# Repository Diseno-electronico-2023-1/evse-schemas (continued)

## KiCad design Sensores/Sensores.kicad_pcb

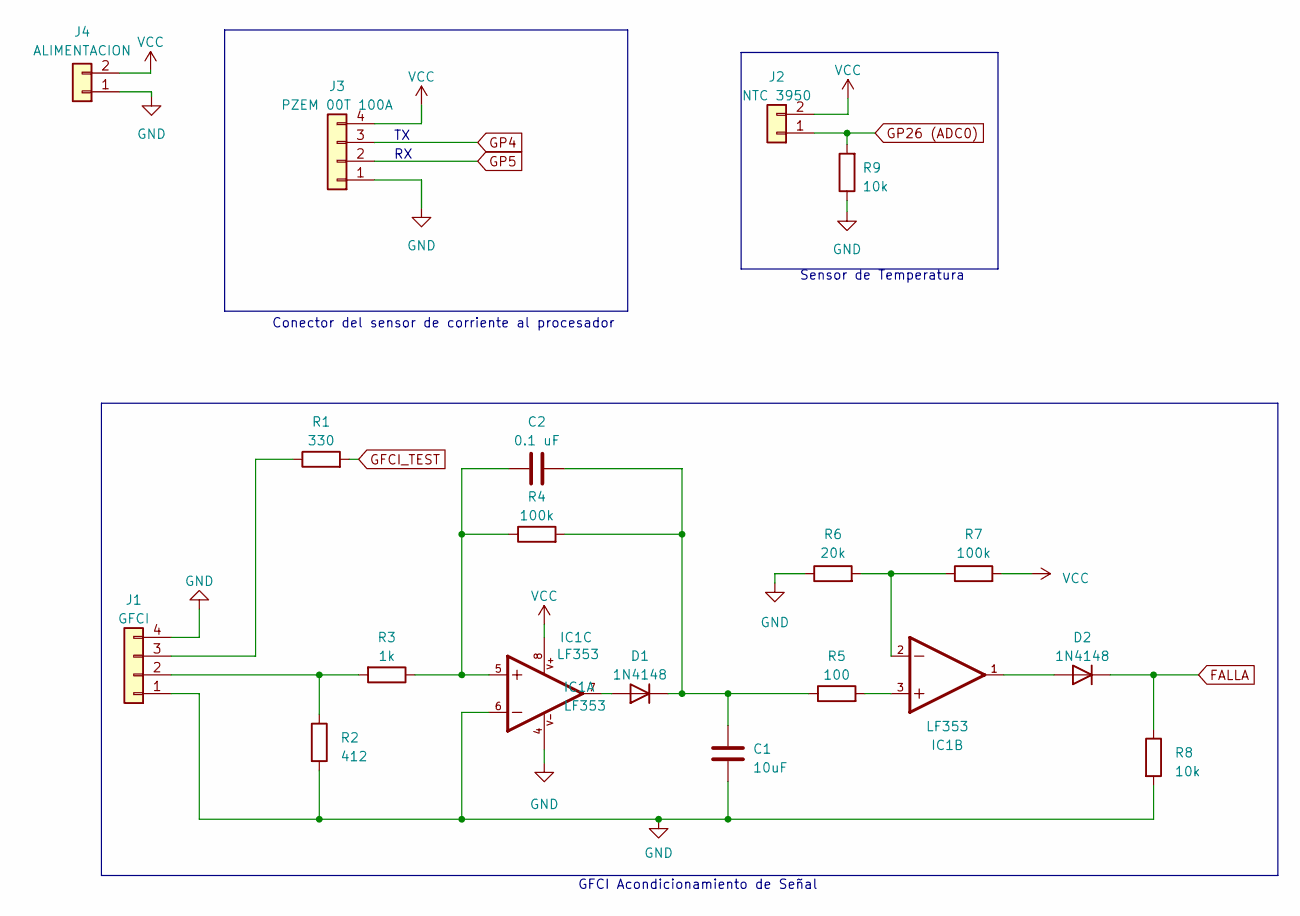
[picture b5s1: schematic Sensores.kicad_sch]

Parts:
C1: 10uF; C_0805_2012Metric_Pad1.18x1.45mm_HandSolder
C2: 0.1 uF; C_0805_2012Metric_Pad1.18x1.45mm_HandSolder
D1, D2: 1N4148; D_DO-35_SOD27_P7.62mm_Horizontal
IC1: LF353; DIL08
J1: GFCI; JST_EH_B4B-EH-A_1x04_P2.50mm_Vertical
J2: NTC 3950; JST_EH_B2B-EH-A_1x02_P2.50mm_Vertical
J3: PZEM 00T 100A; JST_EH_B4B-EH-A_1x04_P2.50mm_Vertical
J4: ALIMENTACION; JST_EH_B2B-EH-A_1x02_P2.50mm_Vertical
R1: 330; R_1206_3216Metric_Pad1.30x1.75mm_HandSolder
R2: 412; R_1206_3216Metric_Pad1.30x1.75mm_HandSolder
R3: 1k; R_1206_3216Metric_Pad1.30x1.75mm_HandSolder
R4, R7: 100k; R_1206_3216Metric_Pad1.30x1.75mm_HandSolder
R5: 100; R_1206_3216Metric_Pad1.30x1.75mm_HandSolder
R6: 20k; R_1206_3216Metric_Pad1.30x1.75mm_HandSolder
R8, R9: 10k; R_1206_3216Metric_Pad1.30x1.75mm_HandSolder

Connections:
FALLA: D2.1 (K), R8.1
GFCI_TEST: R1.2
GND: C1.2, IC1.4, IC1.6, J1.1, J1.4, J3.1, J4.1, R2.2, R6.1, R8.2, R9.1
GP4: J3.3
GP5: J3.2
GP26 (ADC0): J2.1, R9.2
unnamed: C2.1, IC1.5, R3.1, R4.1
unnamed: D1.2 (A), IC1.7
unnamed: C1.1, C2.2, D1.1 (K), R4.2, R5.1
unnamed: D2.2 (A), IC1.1
unnamed: IC1.2, R6.2, R7.1
unnamed: IC1.3, R5.2
unnamed: J1.2, R2.1, R3.2
unnamed: J1.3, R1.1
VCC: IC1.8, J2.2, J3.4, J4.2, R7.2

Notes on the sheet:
GFCI Acondicionamiento de Señal
Sensor de Temperatura
Conector del sensor de corriente al procesador

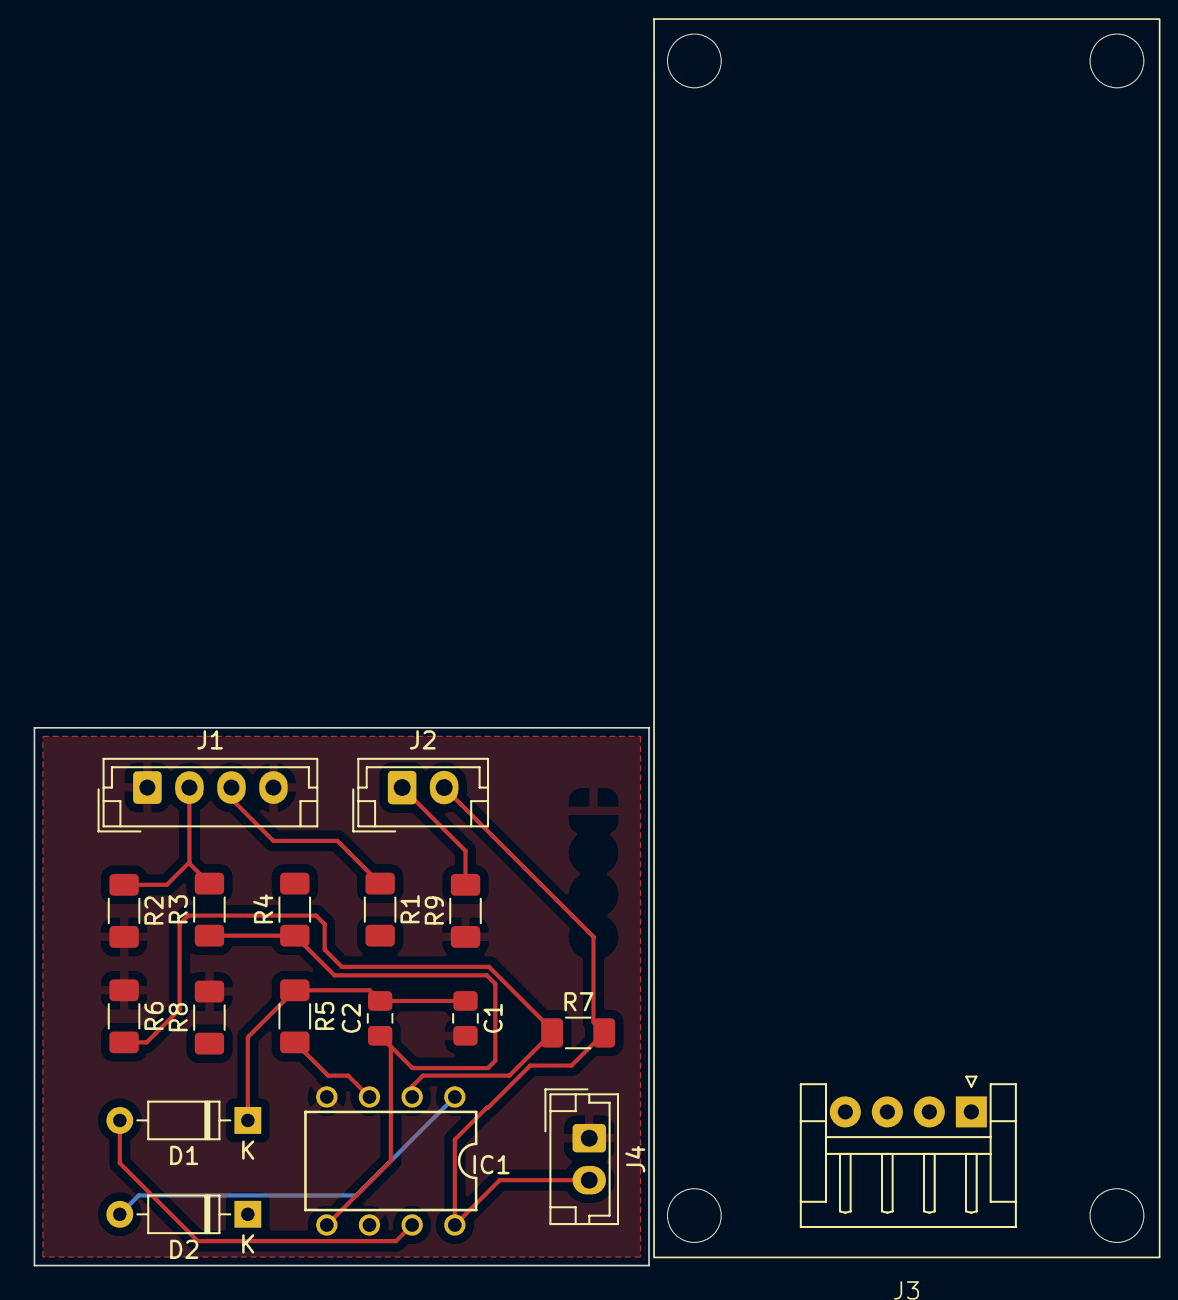
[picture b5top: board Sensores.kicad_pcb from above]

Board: 2 copper layers, 36.6 x 32.0 mm, 18 parts (0 on the bottom side), 12 nets.

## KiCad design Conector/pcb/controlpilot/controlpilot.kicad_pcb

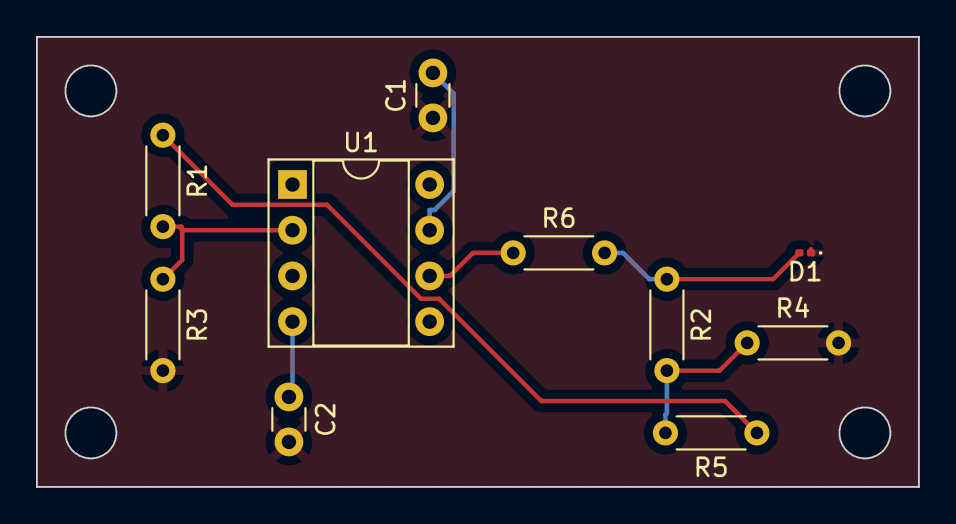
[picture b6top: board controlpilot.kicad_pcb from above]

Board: 2 copper layers, 49.0 x 25.0 mm, 10 parts (0 on the bottom side), 8 nets.

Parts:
C1, C2: 0.1u; C_Disc_D3.0mm_W1.6mm_P2.50mm
D1: PGB1010603NR; LED_0201_0603Metric
R1, R2, R3: 200k; R_Axial_DIN0204_L3.6mm_D1.6mm_P5.08mm_Horizontal
R4: 66.5k; R_Axial_DIN0204_L3.6mm_D1.6mm_P5.08mm_Horizontal
R5: 56k; R_Axial_DIN0204_L3.6mm_D1.6mm_P5.08mm_Horizontal
R6: 1k; R_Axial_DIN0204_L3.6mm_D1.6mm_P5.08mm_Horizontal
U1: LM741; DIP-8_W7.62mm_Socket

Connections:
+3V3: R1.1, R5.1
+12V: C1.2, U1.7 (V+)
-12V: C2.1, U1.4 (V-)
GND: C1.1, C2.2, D1.1 (A1), R3.2, R4.2
unnamed: D1.2 (A2), R2.1, R6.2
unnamed: R2.2, R4.1, R5.2
unnamed: R6.1, U1.6
unnamed: R1.2, R3.1, U1.2 (-)

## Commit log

2023-03-21 Esquemas de potencia
2023-03-21 Create Sensores
2023-03-21 Crictuitos y PCB sensores
2023-03-23 footprint del pzem 004t
2023-03-27 datasheetrp2040
2023-03-27 MicrocontroladorPCB
2023-03-28 Create Pilot Signal
2023-03-28 Se incluye esquema del rp2040
2023-03-28 Footprint Convertidor AC/DC Agregado. Esquemáticos sin errores de Diseño
2023-03-28 Esquemáticos y simulaciones del circuito de comunicaciones
2023-03-28 repositorio i5ether
2023-03-29 actualización huella rp2040
2023-03-29 Bloques_CircuitoPotencia_ControlPilot
2023-03-29 correción de algunas referencias
2023-03-30 potencia
2023-03-30 se añade relé, se corrigen parámetros
2023-03-30 guardado
2023-03-30 Se modifica la ubicación de pines
2023-03-31 Esquemáticos Combinados. Proyecto principal CircuitoPotencia
2023-03-31 Se modifica esquema del micro y se agrega página de sensores
2023-04-11 Potencia_actualiza
2023-04-11 dddd
2023-04-11 Pinout sensores
2023-04-11 Actualización11/04/2023
2023-04-11 Cambio de pantalla
2023-04-11 Actualización de carpeta Control Pilot
2023-04-12 Actualización_huellas_Potencia
2023-04-13 quitando un magnetico
2023-04-13 Huella_Induct
2023-04-18 SS34
2023-04-18 Avances en Huellas
2023-04-18 LibreriasLM2596
2023-04-18 LM2596-HuellaActualizada
2023-04-18 zener sensores con huellas
2023-04-18 Actualización Sensores
2023-04-18 Huellas faltantes: Potencia
2023-04-19 Modificación de la huella del microcontrolador
2023-04-19 Modificación relays
2023-04-19 NuevaHuellaLM2596ADJ
2023-04-19 NuevaHuellaPot
2023-04-20 Cambios de recomendaciones profesor
2023-04-20 H.Pot
2023-04-20 CorrecciónPotencia
2023-04-20 InversorPotencia
2023-04-20 Actualización17.0
2023-04-25 Creación de la PCB - Deben organizarse los componentes
2023-04-25 version inicial layout PCB
2023-05-02 PCB con ruteo realizado. Errores en los anchos de vias -0.2mm. Huella LF356n actualizada
2023-05-03 PCB con Modificaciones de PLanos de Tierra y Huecos de soporte
2023-05-07 Cambio huella J3 embebidos
2023-05-08 ActualizaciónPCB_LogoUNCargador
2023-05-09 PCB_VersiónFinal_HD4K
2023-05-09 PCB_Final
2023-06-03 Actualizacion controlPilot
2023-06-03 Create Images
2023-06-06 Actualizacion
2023-06-08 Delete Conector/3d-Models directory
    Eliminación de archivos antiguos
2023-06-08 Delete Conector/ControlPilotPCB-backups/ControlPilotPCB-2023-03-19_170218 directory
    Eliminación de archivos antiguos
2023-06-08 Delete Conector/ControlPilotPCB-backups/ControlPilotPCB-2023-03-19_171631 directory
    Eliminación de archivos antiguos
2023-06-20 Create pruebas
2023-06-20 Add files via upload
    Pruebas del circuito del control pilot
2023-06-26 FinalPCB
